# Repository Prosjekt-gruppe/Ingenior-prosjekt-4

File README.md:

# Ingeniør-prosjekt IV

## Specs
**Function:** <br>
Search and rescue<br>
**Size:**<br>
28.5cm propeller to opposite propeller<br>
20cmx20cm PCB design FC-controller & PDB <br> 
**Budget:**<br>
3000 Nok

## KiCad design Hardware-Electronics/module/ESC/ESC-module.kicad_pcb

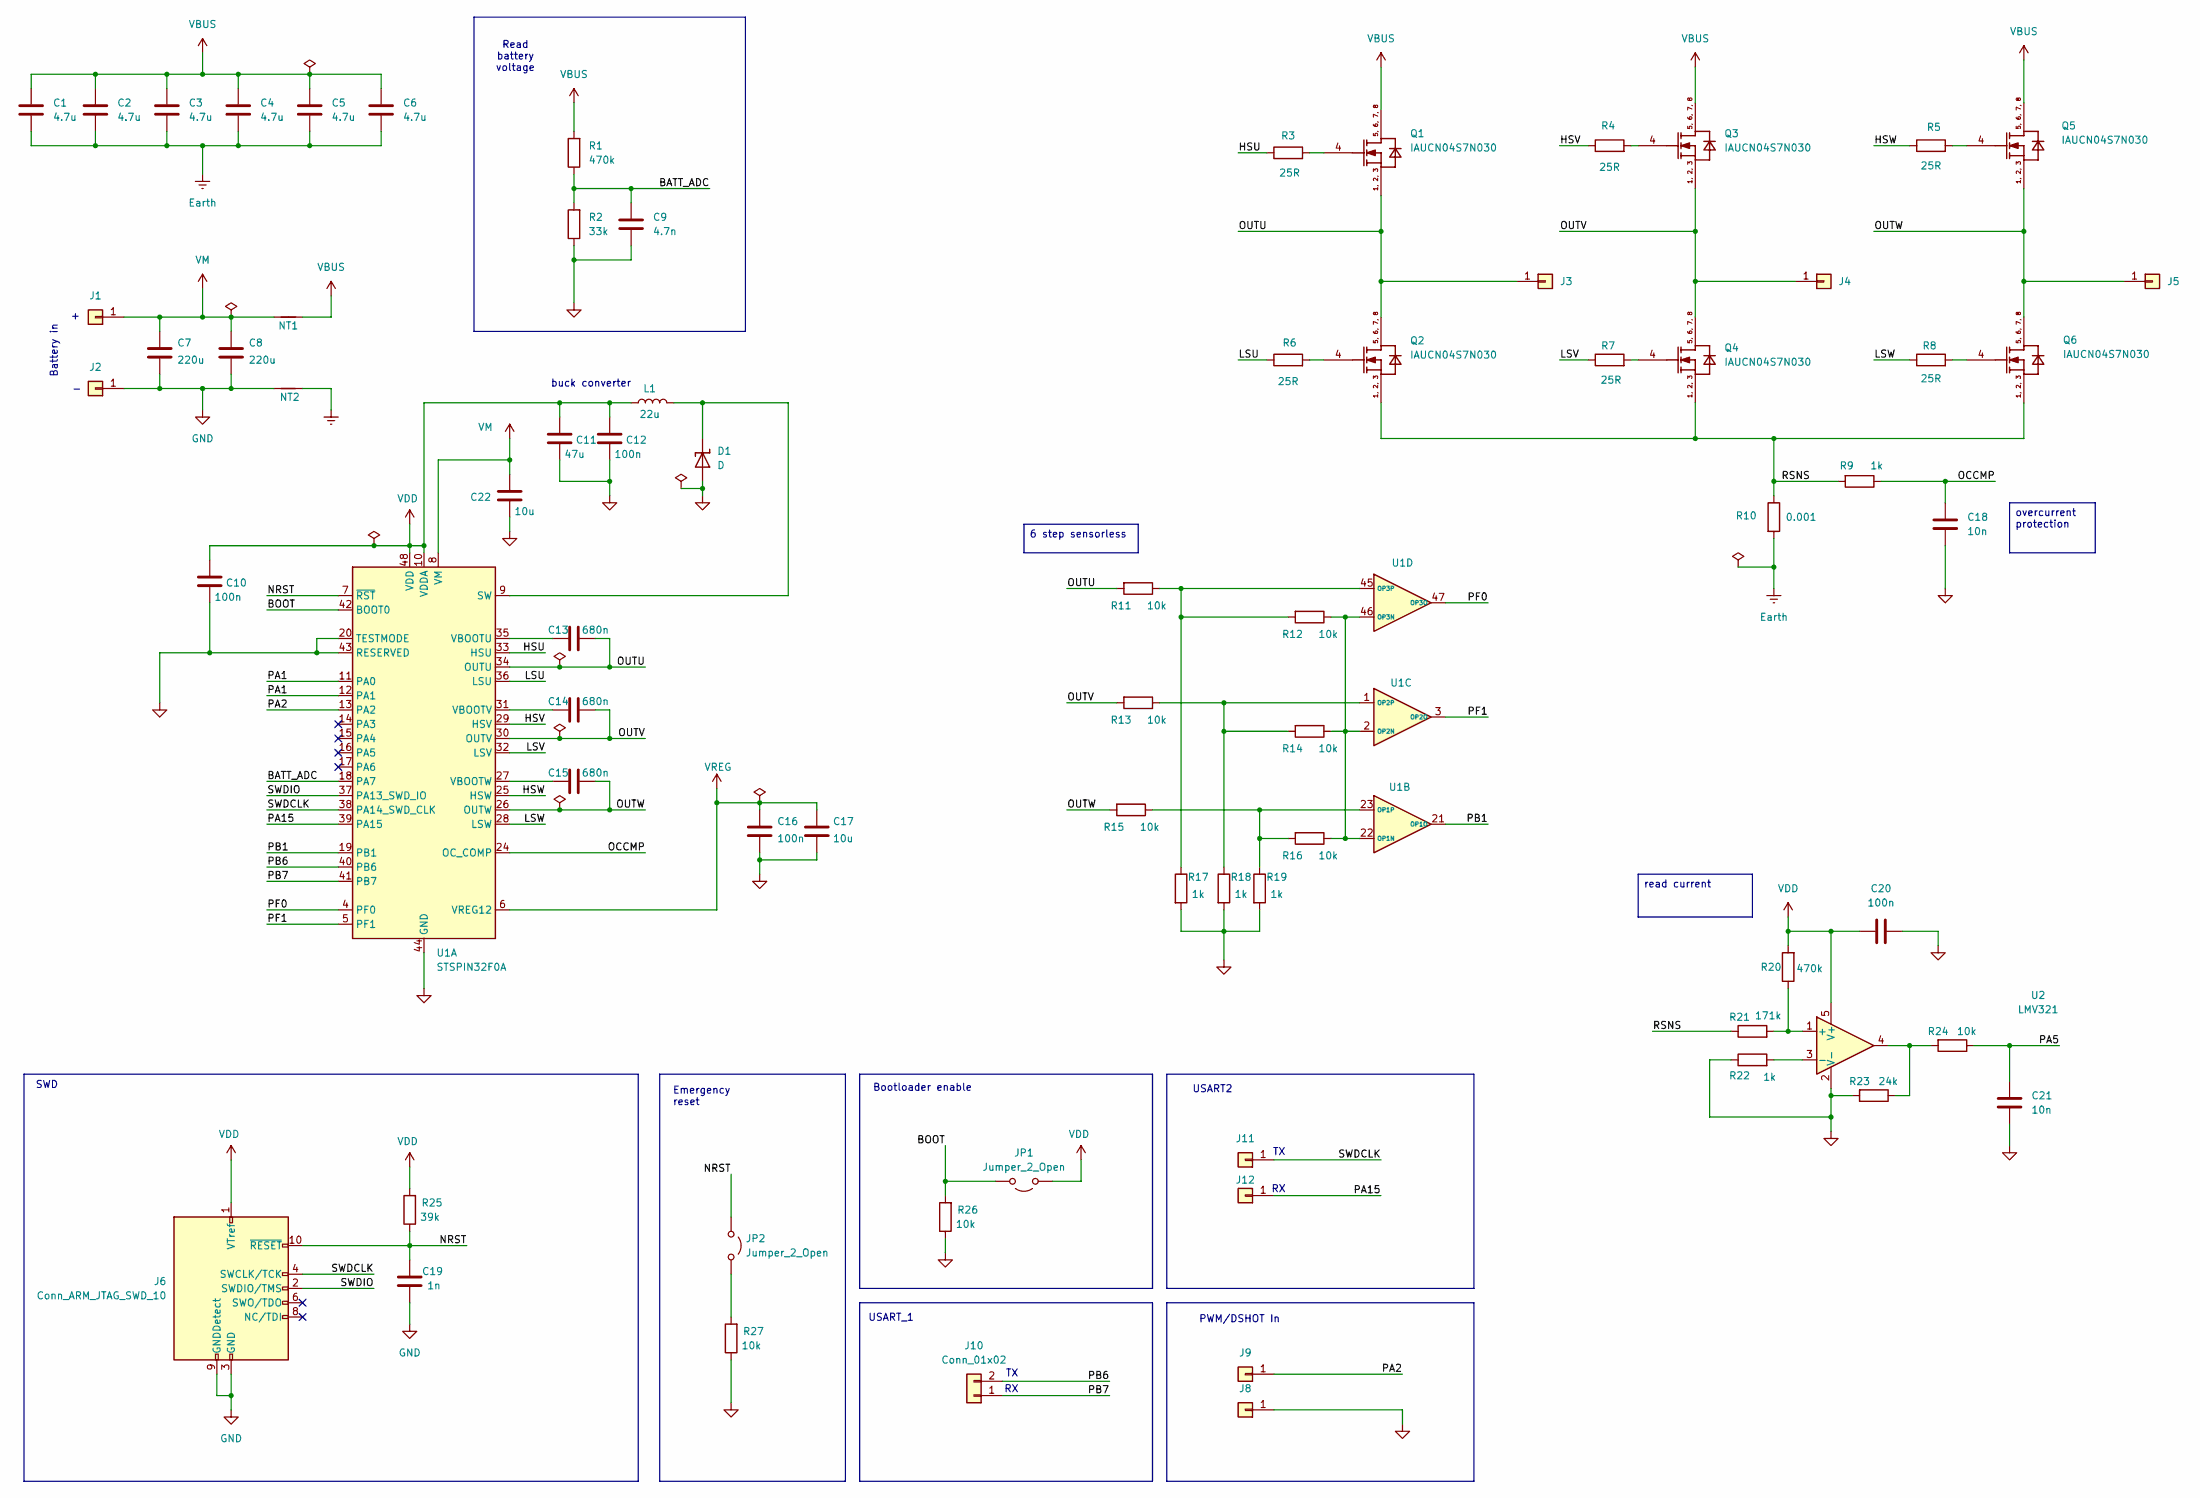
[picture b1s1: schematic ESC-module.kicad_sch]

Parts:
C1, C2, C3, C4, C5, C6: 4.7u; C_0805_2012Metric
C7, C8: 220u
C9: 4.7n; C_0805_2012Metric
C10, C12, C16, C20: 100n; C_0603_1608Metric
C11: 47u; C_0805_2012Metric_Pad1.18x1.45mm_HandSolder
C13, C14, C15: 680n; C_0603_1608Metric
C17: 10u; C_0805_2012Metric
C18, C21: 10n; C_0603_1608Metric
C19: 1n; C_0603_1608Metric
C22: 10u; C_0805_2012Metric_Pad1.18x1.45mm_HandSolder
D1: D
J1, J2, J3, J4, J5: Conn_01x01; SolderWirePad_1x01_SMD_3x6mm
J6: Conn_ARM_JTAG_SWD_10
J8, J9, J11, J12: Conn_01x01; SolderWire-1.5sqmm_1x01_D1.7mm_OD3.9mm
J10: Conn_01x02; PinSocket_1x02_P2.54mm_Vertical
JP1, JP2: Jumper_2_Open; TestPoint_2Pads_Pitch2.54mm_Drill0.8mm
L1: 22u; IND_BOURNS_SRN3015
NT1, NT2: NetTie_2; NetTie-2_SMD_Pad0.5mm
Q1, Q2, Q3, Q4, Q5, Q6: IAUCN04S7N030; INF-PG-TDSON-8-33-V
R1, R20: 470k; R_0603_1608Metric
R2: 33k; R_0603_1608Metric
R3, R4, R5, R6, R7, R8: 25R; R_0603_1608Metric
R9, R17, R18, R19, R22: 1k; R_0603_1608Metric
R10: 0.001; R_Shunt_Vishay_WSR2_WSR3
R11, R12, R13, R14, R15, R16, R24, R26, R27: 10k; R_0603_1608Metric
R21: 171k; R_0603_1608Metric
R23: 24k; R_0603_1608Metric
R25: 39k; R_0603_1608Metric
U1: STSPIN32F0A; VQFN-48-1EP_7x7mm_P0.5mm_EP2.6x2.6mm_with_model
U2: LMV321; SOT-353_SC-70-5_Handsoldering

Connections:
/BATT_ADC: C9.1, R1.1, R2.2, U1.18 (PA7)
/BOOT: JP1.2 (B), R26.2, U1.42 (BOOT0)
/HSU: R3.1, U1.33 (HSU)
/HSV: R4.1, U1.29 (HSV)
/HSW: R5.1, U1.25 (HSW)
/LSU: R6.1, U1.36 (LSU)
/LSV: R7.1, U1.32 (LSV)
/LSW: R8.1, U1.28 (LSW)
/NRST: C19.2, J6.10 (~RESET), JP2.1 (A), R25.1, U1.7 (~RST)
/OCCMP: C18.2, R9.1, U1.24 (OC_COMP)
/OUTU: C13.2, J3.1, Q1.1 (SOURCE), Q1.2 (SOURCE), Q1.3 (SOURCE), Q2.5 (DRAIN), Q2.6 (DRAIN), Q2.7 (DRAIN), Q2.8 (DRAIN), R11.2, U1.34 (OUTU)
/OUTV: C14.2, J4.1, Q3.1 (SOURCE), Q3.2 (SOURCE), Q3.3 (SOURCE), Q4.5 (DRAIN), Q4.6 (DRAIN), Q4.7 (DRAIN), Q4.8 (DRAIN), R13.2, U1.30 (OUTV)
/OUTW: C15.2, J5.1, Q5.1 (SOURCE), Q5.2 (SOURCE), Q5.3 (SOURCE), Q6.5 (DRAIN), Q6.6 (DRAIN), Q6.7 (DRAIN), Q6.8 (DRAIN), R15.2, U1.26 (OUTW)
/PA1: U1.11 (PA0), U1.12 (PA1)
/PA2: J9.1, U1.13 (PA2)
/PA5: C21.1, R24.1
/PA15: J12.1, U1.39 (PA15)
/PB1: U1.19 (PB1), U1.21 (OP1O)
/PB6: J10.2, U1.40 (PB6)
/PB7: J10.1, U1.41 (PB7)
/PF0: U1.4 (PF0), U1.47 (OP3O)
/PF1: U1.3 (OP2O), U1.5 (PF1)
/RSNS: Q2.1 (SOURCE), Q2.2 (SOURCE), Q2.3 (SOURCE), Q4.1 (SOURCE), Q4.2 (SOURCE), Q4.3 (SOURCE), Q6.1 (SOURCE), Q6.2 (SOURCE), Q6.3 (SOURCE), R9.2, R10.1, R21.1
/SWDCLK: J6.4 (SWCLK/TCK), J11.1, U1.38 (PA14_SWD_CLK)
/SWDIO: J6.2 (SWDIO/TMS), U1.37 (PA13_SWD_IO)
Earth: C1.2, C2.2, C3.2, C4.2, C5.2, C6.2, NT2.2, R10.2
GND: C7.1, C8.1, C9.2, C10.2, C11.2, C12.2, C16.1, C17.1, C18.1, C19.1, C20.1, C21.2, C22.2, D1.2 (A), J2.1, J6.3 (GND), J6.5 (GND), J6.9 (GNDDetect), J8.1, NT2.1, R2.1, R17.2, R18.2, R19.2, R22.1, R23.2, R26.1, R27.1, U1.20 (TESTMODE), U1.43 (RESERVED), U1.44 (GND), U1.49 (GND), U2.2 (V-)
unnamed: D1.1 (K), L1.2, U1.9 (SW)
unnamed: JP2.2 (B), R27.2
unnamed: Q1.4 (GATE), R3.2
unnamed: Q2.4 (GATE), R6.2
unnamed: Q3.4 (GATE), R4.2
unnamed: Q4.4 (GATE), R7.2
unnamed: Q5.4 (GATE), R5.2
unnamed: Q6.4 (GATE), R8.2
unnamed: R23.1, R24.2, U2.4
unnamed: C13.1, U1.35 (VBOOTU)
unnamed: C14.1, U1.31 (VBOOTV)
unnamed: C15.1, U1.27 (VBOOTW)
unnamed: R12.1, R14.1, R16.1, U1.2 (OP2N), U1.22 (OP1N), U1.46 (OP3N)
unnamed: R15.1, R16.2, R19.1, U1.23 (OP1P)
unnamed: R13.1, R14.2, R18.1, U1.1 (OP2P)
unnamed: R11.1, R12.2, R17.1, U1.45 (OP3P)
unnamed: R20.1, R21.2, U2.1 (+)
unnamed: R22.2, U2.3 (-)
VBUS: C1.1, C2.1, C3.1, C4.1, C5.1, C6.1, NT1.2, Q1.5 (DRAIN), Q1.6 (DRAIN), Q1.7 (DRAIN), Q1.8 (DRAIN), Q3.5 (DRAIN), Q3.6 (DRAIN), Q3.7 (DRAIN), Q3.8 (DRAIN), Q5.5 (DRAIN), Q5.6 (DRAIN), Q5.7 (DRAIN), Q5.8 (DRAIN), R1.2
VDD: C10.1, C11.1, C12.1, C20.2, J6.1 (VTref), JP1.1 (A), L1.1, R20.2, R25.2, U1.10 (VDDA), U1.48 (VDD), U2.5 (V+)
VM: C7.2, C8.2, C22.1, J1.1, NT1.1, U1.8 (VM)
VREG: C16.2, C17.2, U1.6 (VREG12)

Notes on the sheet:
USART_1
SWD
Emergency reset
Read battery voltage
USART2
Bootloader enable
Battery in
buck converter
PWM/DSHOT In
read current
6 step sensorless
overcurrent protection

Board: 4 copper layers, 70 parts (14 on the bottom side), 48 nets, no tracks yet.

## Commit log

2025-09-02 Add initial README
2025-09-09 Create Documentation
2025-09-09 Create Controller
2025-09-09 Create Firmware
2025-09-09 TEST
2025-09-09 Added Overview FC.drawio
2025-09-09 Change 'Price' to 'Budget' in README
2025-09-09 Created input handling file
2025-09-09 Added Overview FC.png
2025-09-09 Changed from tkinter to pygame for more animatiability
2025-09-11 Added FC-V0 Overview .drawio.png
2025-09-11 Delete Documentation/Drawio-Diagram/Overview FC.drawio
    Bad design
2025-09-11 Delete Documentation/Drawio-Diagram/Overview FC.png
    Bad design
2025-09-15 Added gauges to the ui
2025-09-16 Added Flight Controller
2025-09-16 Added Auto Programmer
2025-09-18 Update README.md
    Added size criteria
2025-09-22 Added communication overview
    A small drawing of what the communication setup will be like.
2025-09-23 Changed gauge design for easier reading and development
2025-09-23 Added heading filling functionality and started work on thrust power integration
2025-09-23 Added: Sensors, Espressif Schematic file and Boot Options
2025-09-25 Added: - New PCB Design - Completed ESP32 configuration comp. - Ran Electrical Rules Check (ERC)
2025-09-30 Add .gitignore for KiCad project files
    Added a comprehensive .gitignore file for KiCad projects, including rules for temporary files, netlist files, autorouter files, footprint association files, exported BOM files, and miscellaneous file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
2025-09-30 Delete Hardware-Electronics/module/Flight-Controller/drone-v0/fp-info-cache
    Deleted cache
2025-09-30 Some changes to gitignore
2025-09-30 Added battery status basis for future integration
2025-09-30 Create LICENSE
2025-09-30 Set up a folder for ELRS
2025-09-30 Add new Buy Me a Coffee username
2025-09-30 Update Buy Me a Coffee usernames format
    Consolidate Buy Me a Coffee usernames into a single line.
2025-10-07 Added basic controller button support and restructured the GUI drawing to make it draw consistently
2025-10-07 Moved some files
2025-10-07 updated gitignore
2025-10-07 same as before
2025-10-07 New communication overview with SX1280
2025-10-11 WTF is ELRS to doing my PC
2025-10-11 Set 2.4GHz EU freq
2025-10-14 Initial schematic for ESC
2025-10-14 Added variables to text view and added controll list in README.md
2025-10-19 Updates: dual LDO power design for STM32F405 flight controller - Added 3V3_MCU and 3V3_SNS rails for noise isolation - Integrated USB-C power input and SWD header - Finalized ESC, IMU, and barometer 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
2025-10-20 Added: STM32
2025-10-20 Apply .gitignore
2025-10-20 Added: STM32 Try resolve with rebase
2025-10-20 Save pending KiCad edits befor PR
2025-10-20 Finishing touches
2025-10-20 Forgot footprint for SWD
2025-10-20 Remove backup files
2025-10-20 Flight Controller updates (rebased) (#20)
    * Updates: dual LDO power design for STM32F405 flight controller
    - Added 3V3_MCU and 3V3_SNS rails for noise isolation
    - Integrated USB-C power input and SWD header
    - Finalized ESC, IMU, and barometer connections
    - Verified power sequencing and decoupling networks
    * Added: STM32 Try resolve with rebase
2025-10-23 Created initla board outline
2025-10-24 Feature/esc initial schematic (#21)
    * Initial schematic for ESC
    * Finishing touches
    * Forgot footprint for SWD
    * Remove backup files
2025-10-28 Controller check at runtime added
2025-10-28 gitignore fixes
2025-10-28 Controller (#16)
    * Initial commit
    * TEST
    * Created input handling file
    * Changed from tkinter to pygame for more animatiability
    * Added gauges to the ui
    * Changed gauge design for easier reading and development
2025-10-28 Changed branch name
2025-10-28 cleaned up other branche's files after pull
2025-10-28 renaming foler back to controller
2025-11-04 Added background for a nicer ux
2025-11-04 Added barometer
2025-11-04 Serial communication between Python and ESP
2025-11-04 Some more
2025-11-04 Super basic serial print
2025-11-04 Test ESP32 sender
2025-11-04 Added random telemetry and full duplex
2025-11-17 Integrated besc seiral code from test file into main file
2025-12-03 Controller branch got messed up and this is the result of those commits
2025-12-03 Publish branch
2025-12-03 Added button logic to smoothly switch between existing and setting views
2025-12-03 added mor logical button namesake for the different views
2025-12-03 Baudrate changing via dropdown menu and connected serialports adre now added
2025-12-03 Basic settings for Com port and baudrate change is fully implemented
2025-12-03 Serial-settings-menu (#24)
    * Publish branch
    * Added button logic to smoothly switch between existing and setting views
    * added mor logical button namesake for the different views
    * Baudrate changing via dropdown menu and connected serialports adre now added
    * Basic settings for Com port and baudrate change is fully implemented
2025-12-03 Lazy implementation of roll gauge, but it works for an mvp
2025-12-03 small change to fix smal mistake
2025-12-06 Added pitch bar animation
2025-12-07 Serial device selection now works
2025-12-07 The UART bridge to code the ESP01F
2025-12-07 Bridge should be working
2025-12-08 Barebone versions of ELRS for development
2025-12-08 Barebones codes
2025-12-08 Now implemented UART JSON + CRSF
2025-12-09 Added JSON
2025-12-09 Fixed RADIOLIB MODEM issue
2025-12-09 Fixed MODEM issue on the TX side too
2025-12-09 Elrs (#26)
    * Super basic serial print
    * Test ESP32 sender
    * Added random telemetry and full duplex
    * The UART bridge to code the ESP01F
    * Bridge should be working
    * Barebone versions of ELRS for development
2025-12-09 Rewritten to be more dynamic and easier to read
2025-12-10 Data streaming toggle is now implemented
2025-12-10 Sending and recieving json format is now implemented, but not tested
2025-12-11 Added lambda80 code
